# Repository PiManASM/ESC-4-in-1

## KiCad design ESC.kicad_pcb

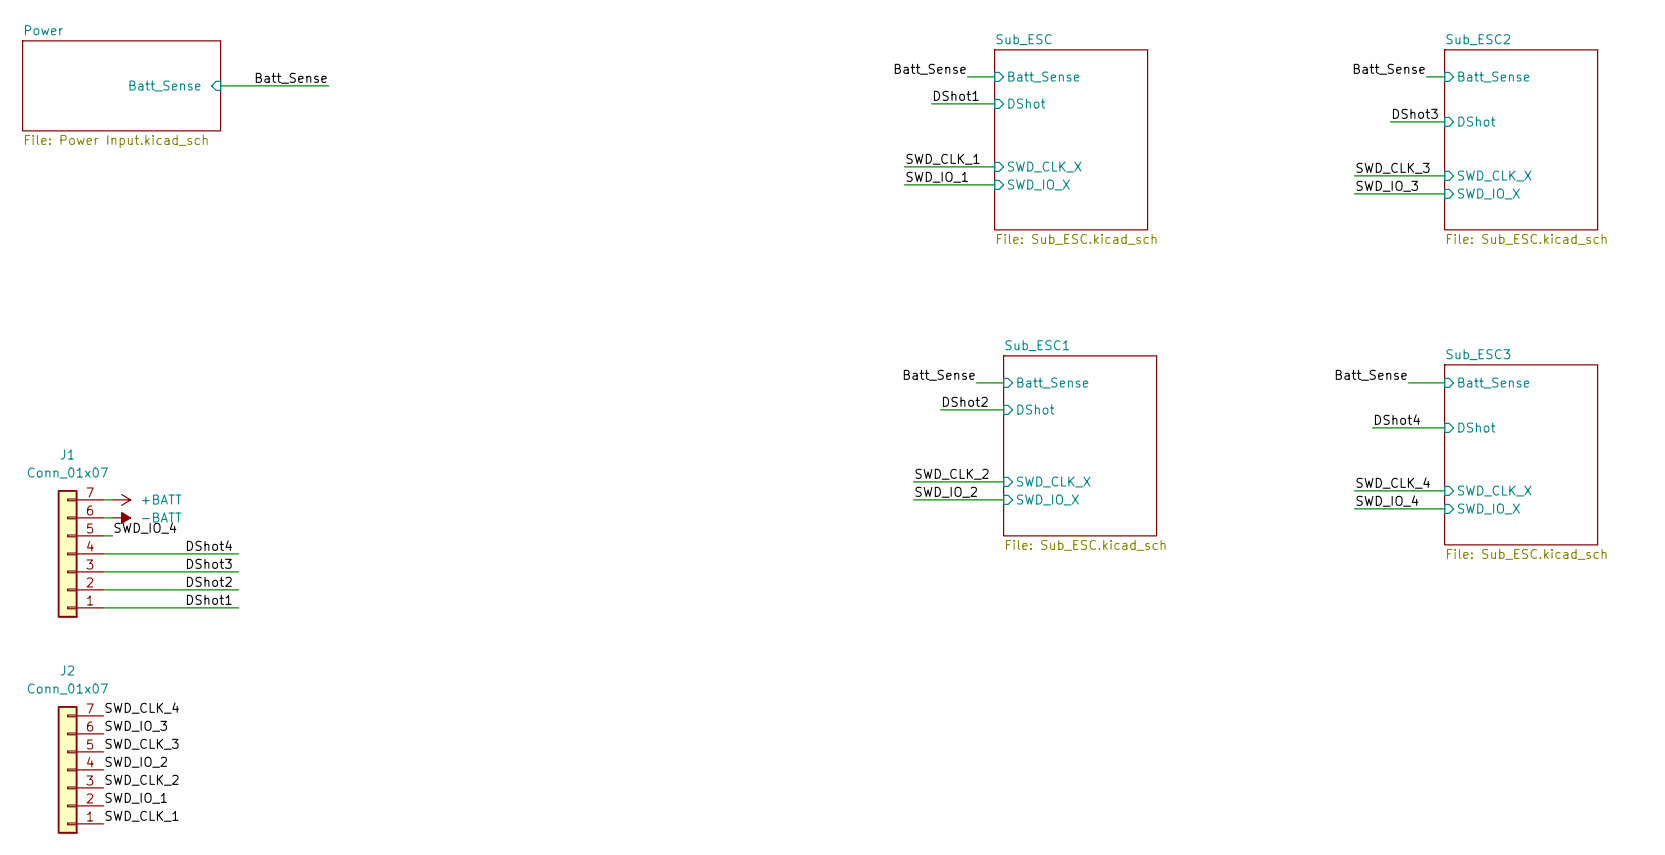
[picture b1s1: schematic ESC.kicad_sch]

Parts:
J1, J2: Conn_01x07; JST_GH_BM07B-GHS-TBT_1x07-1MP_P1.25mm_Vertical

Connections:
-BATT: J1.6; also elsewhere on the board
/DShot1: J1.1; also elsewhere on the board
/DShot2: J1.2; also elsewhere on the board
/DShot3: J1.3; also elsewhere on the board
/DShot4: J1.4; also elsewhere on the board
/SWD_CLK_1: J2.1; also elsewhere on the board
/SWD_CLK_2: J2.3; also elsewhere on the board
/SWD_CLK_3: J2.5; also elsewhere on the board
/SWD_CLK_4: J2.7; also elsewhere on the board
/SWD_IO_1: J2.2; also elsewhere on the board
/SWD_IO_2: J2.4; also elsewhere on the board
/SWD_IO_3: J2.6; also elsewhere on the board
/SWD_IO_4: J1.5; also elsewhere on the board

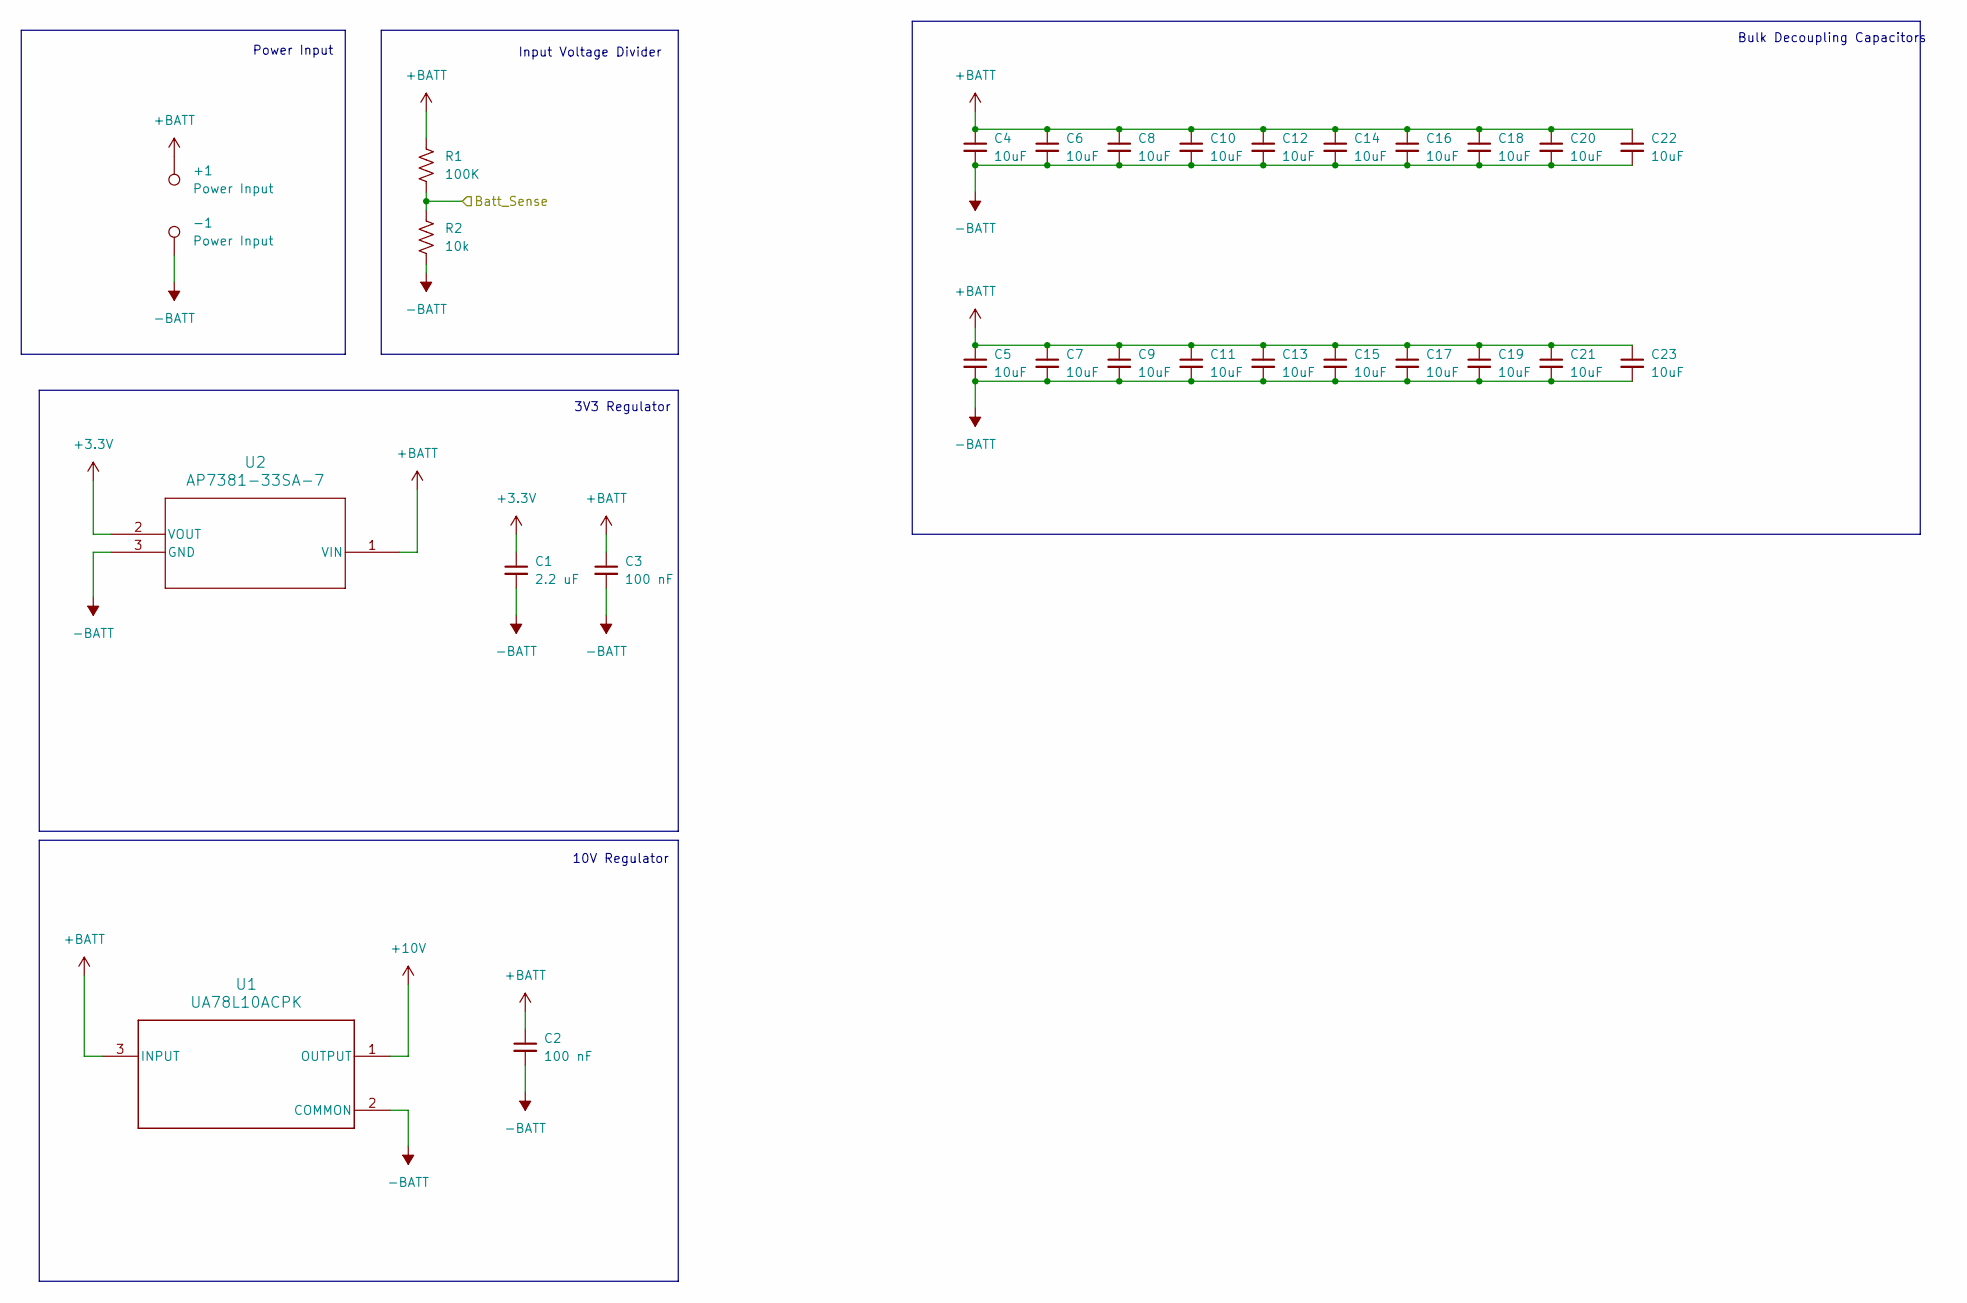
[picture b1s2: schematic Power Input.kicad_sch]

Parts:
+1: Power Input; TestPoint_Pad_4.0x4.0mm
-1: Power Input; TestPoint_Pad_4.0x4.0mm
C1: 2.2 uF; C_0402_1005Metric
C2, C3: 100 nF; C_0402_1005Metric
C4, C5, C6, C7, C8, C9, C10, C11, C12, C13, C14, C15, C16, C17, C18, C19, C20, C21, C22, C23: 10uF; C_0805_2012Metric
R1: 100K; R_0402_1005Metric
R2: 10k; R_0402_1005Metric
U1: UA78L10ACPK; PK0003A_L
U2: AP7381-33SA-7; SOT23_NONCALC_DIO

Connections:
+3.3V: C1.1, U2.2 (VOUT); also elsewhere on the board
-BATT: -1.1, C1.2, C2.2, C3.2, C4.2, C5.2, C6.2, C7.2, C8.2, C9.2, C10.2, C11.2, C12.2, C13.2, C14.2, C15.2, C16.2, C17.2, C18.2, C19.2, C20.2, C21.2, C22.2, C23.2, R2.2, U1.2 (COMMON), U2.3 (GND); also elsewhere on the board
/Batt_Sense: R1.2, R2.1; also elsewhere on the board

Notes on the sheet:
Bulk Decoupling Capacitors
Input Voltage Divider
10V Regulator
Power Input
3V3 Regulator

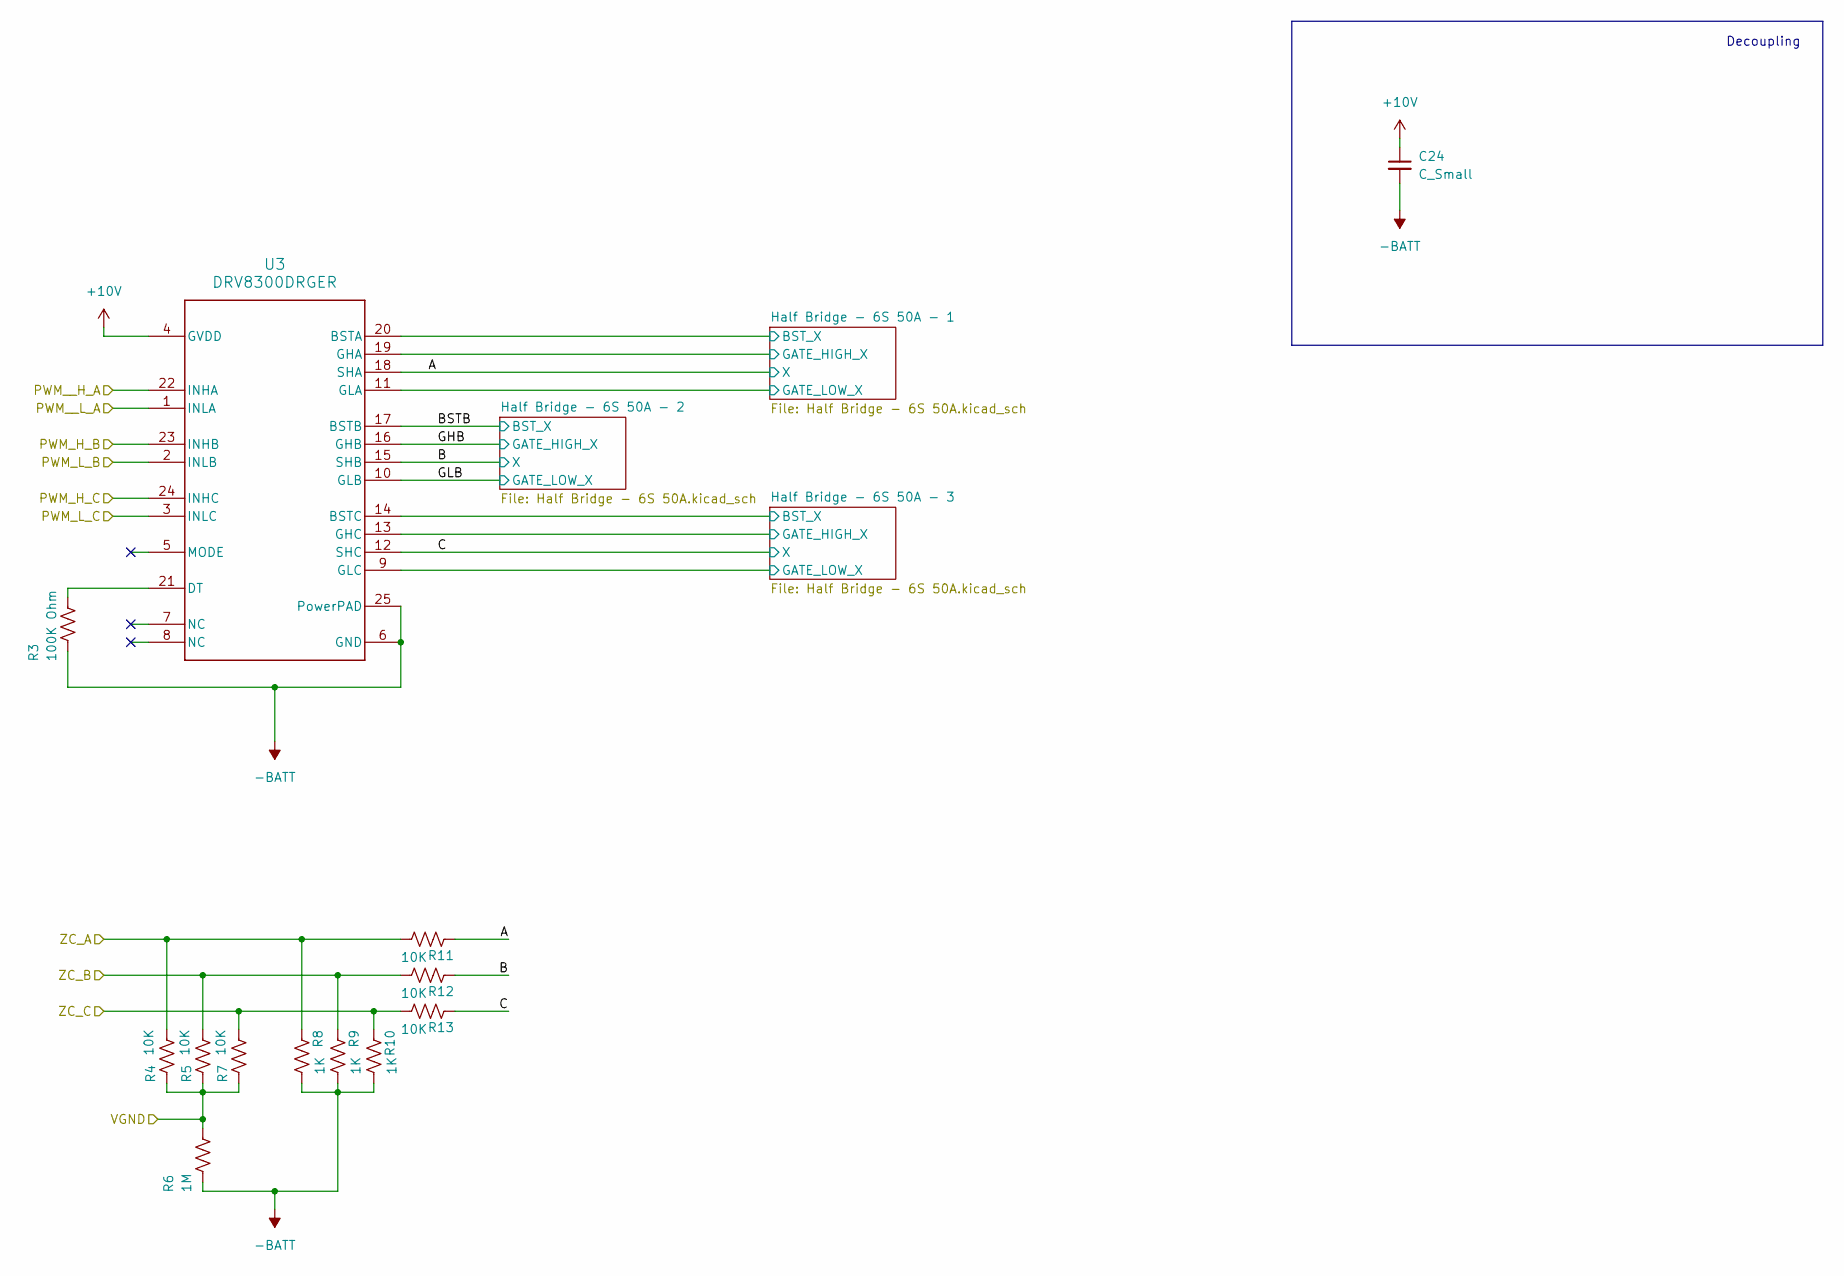
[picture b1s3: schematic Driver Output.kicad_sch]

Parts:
C24: C_Small; C_0603_1608Metric
R3: 100K Ohm; R_0402_1005Metric
R4, R5, R7, R11, R12, R13: 10K; R_0402_1005Metric
R6: 1M; R_0402_1005Metric
R8, R9, R10: 1K; R_0402_1005Metric
U3: DRV8300DRGER; RGE0024B-MFG

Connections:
-BATT: C24.2, R3.2, R6.2, R8.1, R9.1, R10.1, U3.6 (GND), U3.25 (PowerPAD), U3.26, U3.27, U3.28, U3.29, U3.30; also elsewhere on the board
/Sub_ESC/Driver Output/A: R11.2, U3.18 (SHA); also elsewhere on the board
/Sub_ESC/Driver Output/B: R12.2, U3.15 (SHB); also elsewhere on the board
/Sub_ESC/Driver Output/BSTB: U3.17 (BSTB); also elsewhere on the board
/Sub_ESC/Driver Output/C: R13.2, U3.12 (SHC); also elsewhere on the board
/Sub_ESC/Driver Output/GHB: U3.16 (GHB); also elsewhere on the board
/Sub_ESC/Driver Output/GLB: U3.10 (GLB); also elsewhere on the board
/Sub_ESC/Driver Output/Half Bridge - 6S 50A - 1/BST_X: U3.20 (BSTA); also elsewhere on the board
/Sub_ESC/Driver Output/Half Bridge - 6S 50A - 1/GATE_HIGH_X: U3.19 (GHA); also elsewhere on the board
/Sub_ESC/Driver Output/Half Bridge - 6S 50A - 1/GATE_LOW_X: U3.11 (GLA); also elsewhere on the board
/Sub_ESC/Driver Output/Half Bridge - 6S 50A - 3/BST_X: U3.14 (BSTC); also elsewhere on the board
/Sub_ESC/Driver Output/Half Bridge - 6S 50A - 3/GATE_HIGH_X: U3.13 (GHC); also elsewhere on the board
/Sub_ESC/Driver Output/Half Bridge - 6S 50A - 3/GATE_LOW_X: U3.9 (GLC); also elsewhere on the board
/Sub_ESC/Driver Output/PWM_H_B: U3.23 (INHB); also elsewhere on the board
/Sub_ESC/Driver Output/PWM_H_C: U3.24 (INHC); also elsewhere on the board
/Sub_ESC/Driver Output/PWM_L_B: U3.2 (INLB); also elsewhere on the board
/Sub_ESC/Driver Output/PWM_L_C: U3.3 (INLC); also elsewhere on the board
/Sub_ESC/Driver Output/PWM__H_A: U3.22 (INHA); also elsewhere on the board
/Sub_ESC/Driver Output/PWM__L_A: U3.1 (INLA); also elsewhere on the board
/Sub_ESC/Driver Output/ZC_A: R4.1, R8.2, R11.1; also elsewhere on the board
/Sub_ESC/Driver Output/ZC_B: R5.1, R9.2, R12.1; also elsewhere on the board
/Sub_ESC/Driver Output/ZC_C: R7.1, R10.2, R13.1; also elsewhere on the board
/Sub_ESC/VGND: R4.2, R5.2, R6.1, R7.2; also elsewhere on the board
unnamed: R3.1, U3.21 (DT)

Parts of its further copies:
C30, C37, C43: C_Small; C_0603_1608Metric
R16, R29, R42: 100K Ohm; R_0402_1005Metric
R17, R18, R20, R24, R25, R26, R30, R31, R33, R37, R38, R39, R43, R44, R46, R50, R51, R52: 10K; R_0402_1005Metric
R19, R32, R45: 1M; R_0402_1005Metric
R21, R22, R23, R34, R35, R36, R47, R48, R49: 1K; R_0402_1005Metric
U5, U7, U9: DRV8300DRGER; RGE0024B-MFG

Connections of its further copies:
-BATT: C30.2, C37.2, C43.2, R16.2, R19.2, R21.1, R22.1, R23.1, R29.2, R32.2, R34.1, R35.1, R36.1, R42.2, R45.2, R47.1, R48.1, R49.1, U5.6 (GND), U5.25 (PowerPAD), U5.26, U5.27, U5.28, U5.29, U5.30, U7.6 (GND), U7.25 (PowerPAD), U7.26, U7.27, U7.28, U7.29, U7.30, U9.6 (GND), U9.25 (PowerPAD), U9.26, U9.27, U9.28, U9.29, U9.30; also elsewhere on the board
/Sub_ESC1/Driver Output/A: R24.2, U5.18 (SHA); also elsewhere on the board
/Sub_ESC1/Driver Output/B: R25.2, U5.15 (SHB); also elsewhere on the board
/Sub_ESC1/Driver Output/BSTB: U5.17 (BSTB); also elsewhere on the board
/Sub_ESC1/Driver Output/C: R26.2, U5.12 (SHC); also elsewhere on the board
/Sub_ESC1/Driver Output/GHB: U5.16 (GHB); also elsewhere on the board
/Sub_ESC1/Driver Output/GLB: U5.10 (GLB); also elsewhere on the board
/Sub_ESC1/Driver Output/Half Bridge - 6S 50A - 1/BST_X: U5.20 (BSTA); also elsewhere on the board
/Sub_ESC1/Driver Output/Half Bridge - 6S 50A - 1/GATE_HIGH_X: U5.19 (GHA); also elsewhere on the board
/Sub_ESC1/Driver Output/Half Bridge - 6S 50A - 1/GATE_LOW_X: U5.11 (GLA); also elsewhere on the board
/Sub_ESC1/Driver Output/Half Bridge - 6S 50A - 3/BST_X: U5.14 (BSTC); also elsewhere on the board
/Sub_ESC1/Driver Output/Half Bridge - 6S 50A - 3/GATE_HIGH_X: U5.13 (GHC); also elsewhere on the board
/Sub_ESC1/Driver Output/Half Bridge - 6S 50A - 3/GATE_LOW_X: U5.9 (GLC); also elsewhere on the board
/Sub_ESC1/Driver Output/PWM_H_B: U5.23 (INHB); also elsewhere on the board
/Sub_ESC1/Driver Output/PWM_H_C: U5.24 (INHC); also elsewhere on the board
/Sub_ESC1/Driver Output/PWM_L_B: U5.2 (INLB); also elsewhere on the board
/Sub_ESC1/Driver Output/PWM_L_C: U5.3 (INLC); also elsewhere on the board
/Sub_ESC1/Driver Output/PWM__H_A: U5.22 (INHA); also elsewhere on the board
/Sub_ESC1/Driver Output/PWM__L_A: U5.1 (INLA); also elsewhere on the board
/Sub_ESC1/Driver Output/ZC_A: R17.1, R21.2, R24.1; also elsewhere on the board
/Sub_ESC1/Driver Output/ZC_B: R18.1, R22.2, R25.1; also elsewhere on the board
/Sub_ESC1/Driver Output/ZC_C: R20.1, R23.2, R26.1; also elsewhere on the board
/Sub_ESC1/VGND: R17.2, R18.2, R19.1, R20.2; also elsewhere on the board
/Sub_ESC2/Driver Output/A: R37.2, U7.18 (SHA); also elsewhere on the board
/Sub_ESC2/Driver Output/B: R38.2, U7.15 (SHB); also elsewhere on the board
/Sub_ESC2/Driver Output/BSTB: U7.17 (BSTB); also elsewhere on the board
/Sub_ESC2/Driver Output/C: R39.2, U7.12 (SHC); also elsewhere on the board
/Sub_ESC2/Driver Output/GHB: U7.16 (GHB); also elsewhere on the board
/Sub_ESC2/Driver Output/GLB: U7.10 (GLB); also elsewhere on the board
/Sub_ESC2/Driver Output/Half Bridge - 6S 50A - 1/BST_X: U7.20 (BSTA); also elsewhere on the board
/Sub_ESC2/Driver Output/Half Bridge - 6S 50A - 1/GATE_HIGH_X: U7.19 (GHA); also elsewhere on the board
/Sub_ESC2/Driver Output/Half Bridge - 6S 50A - 1/GATE_LOW_X: U7.11 (GLA); also elsewhere on the board
/Sub_ESC2/Driver Output/Half Bridge - 6S 50A - 3/BST_X: U7.14 (BSTC); also elsewhere on the board
/Sub_ESC2/Driver Output/Half Bridge - 6S 50A - 3/GATE_HIGH_X: U7.13 (GHC); also elsewhere on the board
/Sub_ESC2/Driver Output/Half Bridge - 6S 50A - 3/GATE_LOW_X: U7.9 (GLC); also elsewhere on the board
/Sub_ESC2/Driver Output/PWM_H_B: U7.23 (INHB); also elsewhere on the board
/Sub_ESC2/Driver Output/PWM_H_C: U7.24 (INHC); also elsewhere on the board
/Sub_ESC2/Driver Output/PWM_L_B: U7.2 (INLB); also elsewhere on the board
/Sub_ESC2/Driver Output/PWM_L_C: U7.3 (INLC); also elsewhere on the board
/Sub_ESC2/Driver Output/PWM__H_A: U7.22 (INHA); also elsewhere on the board
/Sub_ESC2/Driver Output/PWM__L_A: U7.1 (INLA); also elsewhere on the board
/Sub_ESC2/Driver Output/ZC_A: R30.1, R34.2, R37.1; also elsewhere on the board
/Sub_ESC2/Driver Output/ZC_B: R31.1, R35.2, R38.1; also elsewhere on the board
/Sub_ESC2/Driver Output/ZC_C: R33.1, R36.2, R39.1; also elsewhere on the board
/Sub_ESC2/VGND: R30.2, R31.2, R32.1, R33.2; also elsewhere on the board
/Sub_ESC3/Driver Output/A: R50.2, U9.18 (SHA); also elsewhere on the board
/Sub_ESC3/Driver Output/B: R51.2, U9.15 (SHB); also elsewhere on the board
/Sub_ESC3/Driver Output/BSTB: U9.17 (BSTB); also elsewhere on the board
/Sub_ESC3/Driver Output/C: R52.2, U9.12 (SHC); also elsewhere on the board
/Sub_ESC3/Driver Output/GHB: U9.16 (GHB); also elsewhere on the board
/Sub_ESC3/Driver Output/GLB: U9.10 (GLB); also elsewhere on the board
/Sub_ESC3/Driver Output/Half Bridge - 6S 50A - 1/BST_X: U9.20 (BSTA); also elsewhere on the board
/Sub_ESC3/Driver Output/Half Bridge - 6S 50A - 1/GATE_HIGH_X: U9.19 (GHA); also elsewhere on the board
/Sub_ESC3/Driver Output/Half Bridge - 6S 50A - 1/GATE_LOW_X: U9.11 (GLA); also elsewhere on the board
/Sub_ESC3/Driver Output/Half Bridge - 6S 50A - 3/BST_X: U9.14 (BSTC); also elsewhere on the board
/Sub_ESC3/Driver Output/Half Bridge - 6S 50A - 3/GATE_HIGH_X: U9.13 (GHC); also elsewhere on the board
/Sub_ESC3/Driver Output/Half Bridge - 6S 50A - 3/GATE_LOW_X: U9.9 (GLC); also elsewhere on the board
/Sub_ESC3/Driver Output/PWM_H_B: U9.23 (INHB); also elsewhere on the board
/Sub_ESC3/Driver Output/PWM_H_C: U9.24 (INHC); also elsewhere on the board
/Sub_ESC3/Driver Output/PWM_L_B: U9.2 (INLB); also elsewhere on the board
/Sub_ESC3/Driver Output/PWM_L_C: U9.3 (INLC); also elsewhere on the board
/Sub_ESC3/Driver Output/PWM__H_A: U9.22 (INHA); also elsewhere on the board
/Sub_ESC3/Driver Output/PWM__L_A: U9.1 (INLA); also elsewhere on the board
/Sub_ESC3/Driver Output/ZC_A: R43.1, R47.2, R50.1; also elsewhere on the board
/Sub_ESC3/Driver Output/ZC_B: R44.1, R48.2, R51.1; also elsewhere on the board
/Sub_ESC3/Driver Output/ZC_C: R46.1, R49.2, R52.1; also elsewhere on the board
/Sub_ESC3/VGND: R43.2, R44.2, R45.1, R46.2; also elsewhere on the board
unnamed: R16.1, U5.21 (DT)
unnamed: R29.1, U7.21 (DT)
unnamed: R42.1, U9.21 (DT)

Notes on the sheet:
Decoupling

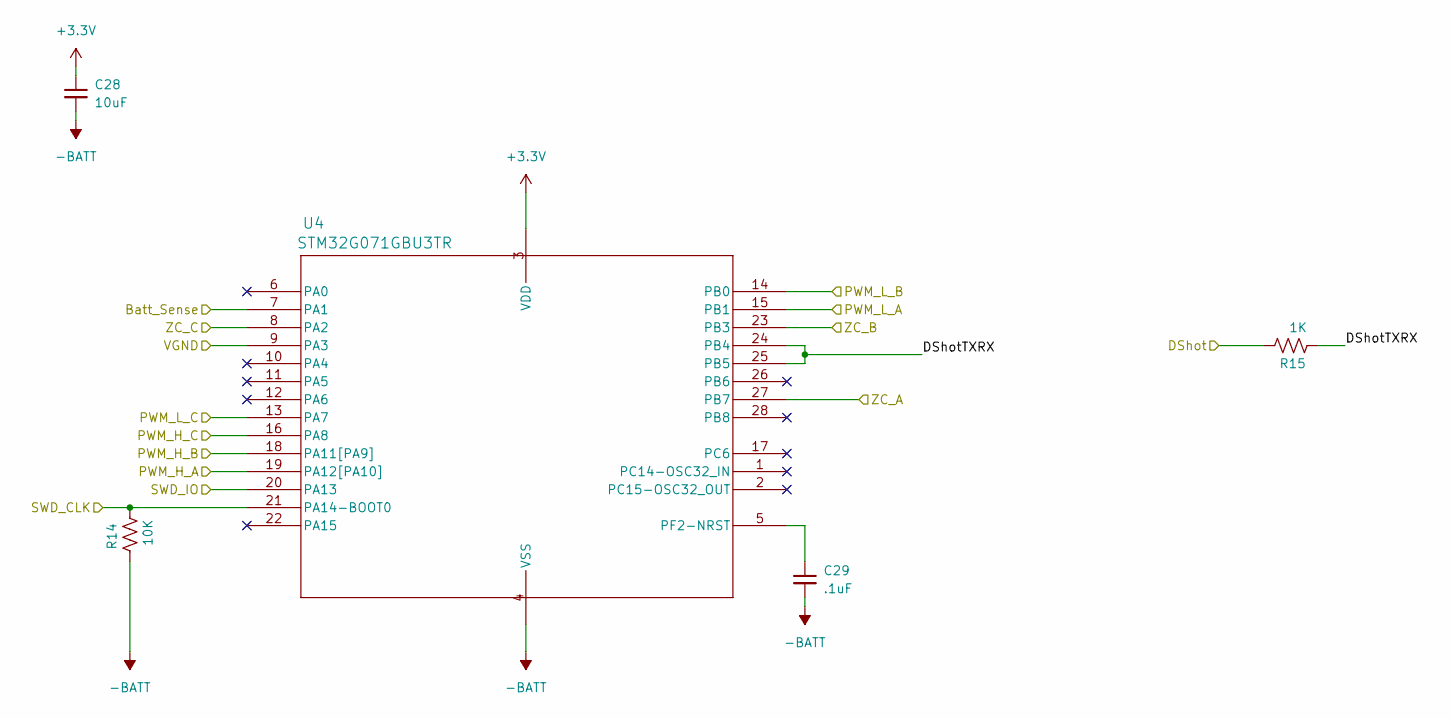
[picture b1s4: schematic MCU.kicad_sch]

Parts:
C28: 10uF; C_0402_1005Metric
C29: .1uF; C_0402_1005Metric
R14: 10K; R_0402_1005Metric
R15: 1K; R_0402_1005Metric
U4: STM32G071GBU3TR; UFQFPN-28

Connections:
+3.3V: C28.1, U4.3 (VDD); also elsewhere on the board
-BATT: C28.2, C29.2, R14.1, U4.4 (VSS); also elsewhere on the board
/Batt_Sense: U4.7 (PA1); also elsewhere on the board
/DShot1: R15.2; also elsewhere on the board
/SWD_CLK_1: R14.2, U4.21 (PA14-BOOT0); also elsewhere on the board
/SWD_IO_1: U4.20 (PA13); also elsewhere on the board
/Sub_ESC/Driver Output/PWM_H_B: U4.18 (PA11[PA9]); also elsewhere on the board
/Sub_ESC/Driver Output/PWM_H_C: U4.16 (PA8); also elsewhere on the board
/Sub_ESC/Driver Output/PWM_L_B: U4.14 (PB0); also elsewhere on the board
/Sub_ESC/Driver Output/PWM_L_C: U4.13 (PA7); also elsewhere on the board
/Sub_ESC/Driver Output/PWM__H_A: U4.19 (PA12[PA10]); also elsewhere on the board
/Sub_ESC/Driver Output/PWM__L_A: U4.15 (PB1); also elsewhere on the board
/Sub_ESC/Driver Output/ZC_A: U4.27 (PB7); also elsewhere on the board
/Sub_ESC/Driver Output/ZC_B: U4.23 (PB3); also elsewhere on the board
/Sub_ESC/Driver Output/ZC_C: U4.8 (PA2); also elsewhere on the board
/Sub_ESC/MCU/DShotTXRX: R15.1, U4.24 (PB4), U4.25 (PB5)
/Sub_ESC/VGND: U4.9 (PA3); also elsewhere on the board
unnamed: C29.1, U4.5 (PF2-NRST)

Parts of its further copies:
C35, C41, C47: 10uF; C_0402_1005Metric
C36, C42, C48: .1uF; C_0402_1005Metric
R27, R40, R53: 10K; R_0402_1005Metric
R28, R41, R54: 1K; R_0402_1005Metric
U6, U8, U10: STM32G071GBU3TR; UFQFPN-28

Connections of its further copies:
+3.3V: C35.1, C41.1, C47.1, U6.3 (VDD), U8.3 (VDD), U10.3 (VDD); also elsewhere on the board
-BATT: C35.2, C36.2, C41.2, C42.2, C47.2, C48.2, R27.1, R40.1, R53.1, U6.4 (VSS), U8.4 (VSS), U10.4 (VSS); also elsewhere on the board
/Batt_Sense: U6.7 (PA1), U8.7 (PA1), U10.7 (PA1); also elsewhere on the board
/DShot2: R28.2; also elsewhere on the board
/DShot3: R41.2; also elsewhere on the board
/DShot4: R54.2; also elsewhere on the board
/SWD_CLK_2: R27.2, U6.21 (PA14-BOOT0); also elsewhere on the board
/SWD_CLK_3: R40.2, U8.21 (PA14-BOOT0); also elsewhere on the board
/SWD_CLK_4: R53.2, U10.21 (PA14-BOOT0); also elsewhere on the board
/SWD_IO_2: U6.20 (PA13); also elsewhere on the board
/SWD_IO_3: U8.20 (PA13); also elsewhere on the board
/SWD_IO_4: U10.20 (PA13); also elsewhere on the board
/Sub_ESC1/Driver Output/PWM_H_B: U6.18 (PA11[PA9]); also elsewhere on the board
/Sub_ESC1/Driver Output/PWM_H_C: U6.16 (PA8); also elsewhere on the board
/Sub_ESC1/Driver Output/PWM_L_B: U6.14 (PB0); also elsewhere on the board
/Sub_ESC1/Driver Output/PWM_L_C: U6.13 (PA7); also elsewhere on the board
/Sub_ESC1/Driver Output/PWM__H_A: U6.19 (PA12[PA10]); also elsewhere on the board
/Sub_ESC1/Driver Output/PWM__L_A: U6.15 (PB1); also elsewhere on the board
/Sub_ESC1/Driver Output/ZC_A: U6.27 (PB7); also elsewhere on the board
/Sub_ESC1/Driver Output/ZC_B: U6.23 (PB3); also elsewhere on the board
/Sub_ESC1/Driver Output/ZC_C: U6.8 (PA2); also elsewhere on the board
/Sub_ESC1/MCU/DShotTXRX: R28.1, U6.24 (PB4), U6.25 (PB5)
/Sub_ESC1/VGND: U6.9 (PA3); also elsewhere on the board
/Sub_ESC2/Driver Output/PWM_H_B: U8.18 (PA11[PA9]); also elsewhere on the board
/Sub_ESC2/Driver Output/PWM_H_C: U8.16 (PA8); also elsewhere on the board
/Sub_ESC2/Driver Output/PWM_L_B: U8.14 (PB0); also elsewhere on the board
/Sub_ESC2/Driver Output/PWM_L_C: U8.13 (PA7); also elsewhere on the board
/Sub_ESC2/Driver Output/PWM__H_A: U8.19 (PA12[PA10]); also elsewhere on the board
/Sub_ESC2/Driver Output/PWM__L_A: U8.15 (PB1); also elsewhere on the board
/Sub_ESC2/Driver Output/ZC_A: U8.27 (PB7); also elsewhere on the board
/Sub_ESC2/Driver Output/ZC_B: U8.23 (PB3); also elsewhere on the board
/Sub_ESC2/Driver Output/ZC_C: U8.8 (PA2); also elsewhere on the board
/Sub_ESC2/MCU/DShotTXRX: R41.1, U8.24 (PB4), U8.25 (PB5)
/Sub_ESC2/VGND: U8.9 (PA3); also elsewhere on the board
/Sub_ESC3/Driver Output/PWM_H_B: U10.18 (PA11[PA9]); also elsewhere on the board
/Sub_ESC3/Driver Output/PWM_H_C: U10.16 (PA8); also elsewhere on the board
/Sub_ESC3/Driver Output/PWM_L_B: U10.14 (PB0); also elsewhere on the board
/Sub_ESC3/Driver Output/PWM_L_C: U10.13 (PA7); also elsewhere on the board
/Sub_ESC3/Driver Output/PWM__H_A: U10.19 (PA12[PA10]); also elsewhere on the board
/Sub_ESC3/Driver Output/PWM__L_A: U10.15 (PB1); also elsewhere on the board
/Sub_ESC3/Driver Output/ZC_A: U10.27 (PB7); also elsewhere on the board
/Sub_ESC3/Driver Output/ZC_B: U10.23 (PB3); also elsewhere on the board
/Sub_ESC3/Driver Output/ZC_C: U10.8 (PA2); also elsewhere on the board
/Sub_ESC3/MCU/DShotTXRX: R54.1, U10.24 (PB4), U10.25 (PB5)
/Sub_ESC3/VGND: U10.9 (PA3); also elsewhere on the board
unnamed: C36.1, U6.5 (PF2-NRST)
unnamed: C42.1, U8.5 (PF2-NRST)
unnamed: C48.1, U10.5 (PF2-NRST)

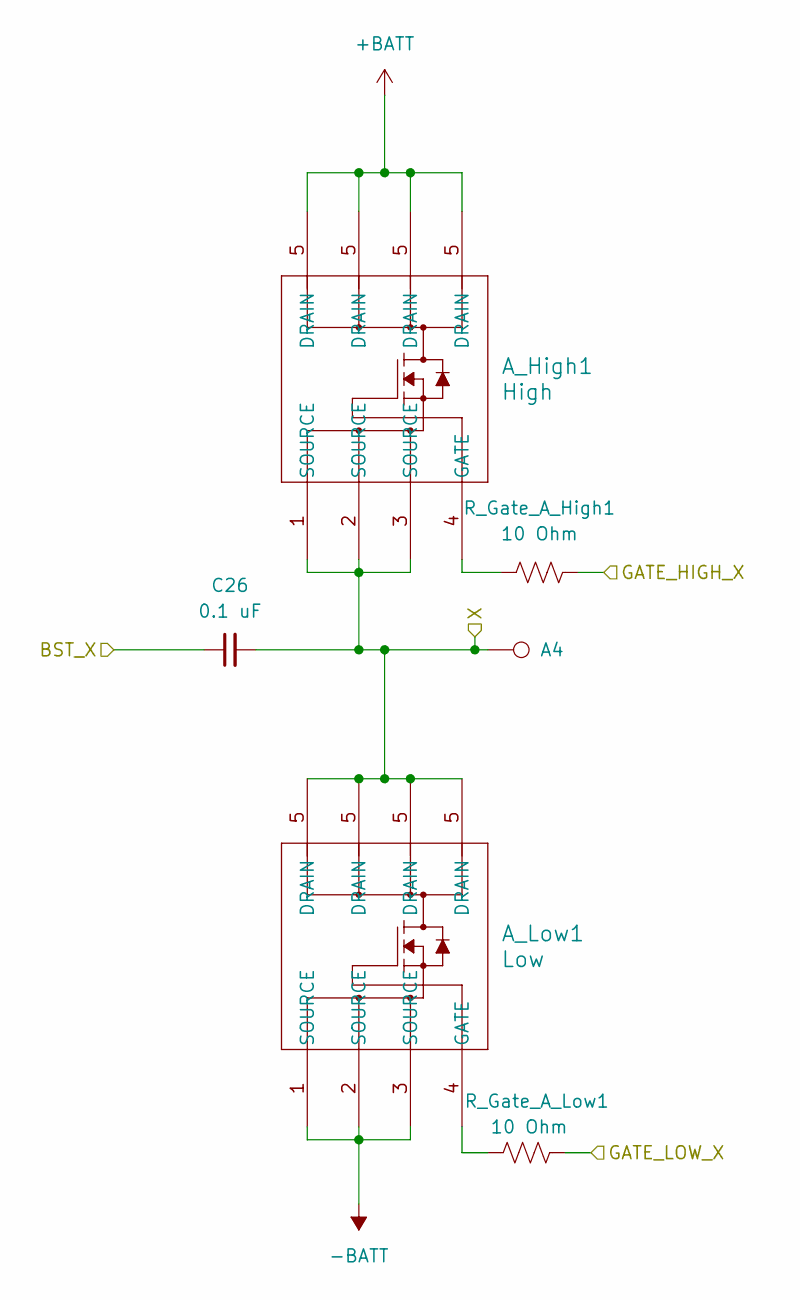
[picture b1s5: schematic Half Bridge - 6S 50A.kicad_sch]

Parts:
A4: TestPoint; TestPoint_Pad_3.5x2.0mm
A_High1: High; SOP-ADVANCE_N_TOS
A_Low1: Low; SOP-ADVANCE_N_TOS
C26: 0.1 uF; C_0402_1005Metric
R_Gate_A_High1: 10 Ohm; R_0402_1005Metric
R_Gate_A_Low1: 10 Ohm; R_0402_1005Metric

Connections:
-BATT: A_Low1.1 (SOURCE), A_Low1.2 (SOURCE), A_Low1.3 (SOURCE); also elsewhere on the board
/Sub_ESC/Driver Output/A: A_High1.1 (SOURCE), A_High1.2 (SOURCE), A_High1.3 (SOURCE), A_Low1.5 (DRAIN), C26.2; also elsewhere on the board
/Sub_ESC/Driver Output/Half Bridge - 6S 50A - 1/BST_X: C26.1; also elsewhere on the board
/Sub_ESC/Driver Output/Half Bridge - 6S 50A - 1/GATE_HIGH_X: R_Gate_A_High1.1; also elsewhere on the board
/Sub_ESC/Driver Output/Half Bridge - 6S 50A - 1/GATE_LOW_X: R_Gate_A_Low1.1; also elsewhere on the board
unnamed: A_High1.4 (GATE), R_Gate_A_High1.2
unnamed: A_Low1.4 (GATE), R_Gate_A_Low1.2

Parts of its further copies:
A1, A2, A3: TestPoint; TestPoint_Pad_3.5x2.0mm
A_High2, A_High3, A_High4: High; SOP-ADVANCE_N_TOS
A_Low2, A_Low3, A_Low4: Low; SOP-ADVANCE_N_TOS
B_High1, B_High2, B_High3, B_High4: High; SOP-ADVANCE_N_TOS
B_Low1, B_Low2, B_Low3, B_Low4: Low; SOP-ADVANCE_N_TOS
C25, C27, C31, C32, C34, C38, C39, C40, C44, C45, C46: 0.1 uF; C_0402_1005Metric
C_High1, C_High2, C_High3, C_High4: High; SOP-ADVANCE_N_TOS
C_Low1, C_Low2, C_Low3, C_Low4: Low; SOP-ADVANCE_N_TOS
R_Gate_A_High2, R_Gate_A_High3, R_Gate_A_High4: 10 Ohm; R_0402_1005Metric
R_Gate_A_Low2, R_Gate_A_Low3, R_Gate_A_Low4: 10 Ohm; R_0402_1005Metric
R_Gate_B_High1, R_Gate_B_High2, R_Gate_B_High3, R_Gate_B_High4: 10 Ohm; R_0402_1005Metric
R_Gate_B_Low1, R_Gate_B_Low2, R_Gate_B_Low3, R_Gate_B_Low4: 10 Ohm; R_0402_1005Metric
R_Gate_C_High1, R_Gate_C_High2, R_Gate_C_High3, R_Gate_C_High4: 10 Ohm; R_0402_1005Metric
R_Gate_C_Low1, R_Gate_C_Low2, R_Gate_C_Low3, R_Gate_C_Low4: 10 Ohm; R_0402_1005Metric

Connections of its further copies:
-BATT: A_Low2.1 (SOURCE), A_Low2.2 (SOURCE), A_Low2.3 (SOURCE), A_Low3.1 (SOURCE), A_Low3.2 (SOURCE), A_Low3.3 (SOURCE), A_Low4.1 (SOURCE), A_Low4.2 (SOURCE), A_Low4.3 (SOURCE), B_Low1.1 (SOURCE), B_Low1.2 (SOURCE), B_Low1.3 (SOURCE), B_Low2.1 (SOURCE), B_Low2.2 (SOURCE), B_Low2.3 (SOURCE), B_Low3.1 (SOURCE), B_Low3.2 (SOURCE), B_Low3.3 (SOURCE), B_Low4.1 (SOURCE), B_Low4.2 (SOURCE), B_Low4.3 (SOURCE), C_Low1.1 (SOURCE), C_Low1.2 (SOURCE), C_Low1.3 (SOURCE), C_Low2.1 (SOURCE), C_Low2.2 (SOURCE), C_Low2.3 (SOURCE), C_Low3.1 (SOURCE), C_Low3.2 (SOURCE), C_Low3.3 (SOURCE), C_Low4.1 (SOURCE), C_Low4.2 (SOURCE), C_Low4.3 (SOURCE); also elsewhere on the board
/Sub_ESC1/Driver Output/A: A_High2.1 (SOURCE), A_High2.2 (SOURCE), A_High2.3 (SOURCE), A_Low2.5 (DRAIN), C31.2; also elsewhere on the board
/Sub_ESC1/Driver Output/B: B_High2.1 (SOURCE), B_High2.2 (SOURCE), B_High2.3 (SOURCE), B_Low2.5 (DRAIN), C34.2; also elsewhere on the board
/Sub_ESC1/Driver Output/BSTB: C34.1; also elsewhere on the board
/Sub_ESC1/Driver Output/C: C32.2, C_High2.1 (SOURCE), C_High2.2 (SOURCE), C_High2.3 (SOURCE), C_Low2.5 (DRAIN); also elsewhere on the board
/Sub_ESC1/Driver Output/GHB: R_Gate_B_High2.1; also elsewhere on the board
/Sub_ESC1/Driver Output/GLB: R_Gate_B_Low2.1; also elsewhere on the board
/Sub_ESC1/Driver Output/Half Bridge - 6S 50A - 1/BST_X: C31.1; also elsewhere on the board
/Sub_ESC1/Driver Output/Half Bridge - 6S 50A - 1/GATE_HIGH_X: R_Gate_A_High2.1; also elsewhere on the board
/Sub_ESC1/Driver Output/Half Bridge - 6S 50A - 1/GATE_LOW_X: R_Gate_A_Low2.1; also elsewhere on the board
/Sub_ESC1/Driver Output/Half Bridge - 6S 50A - 3/BST_X: C32.1; also elsewhere on the board
/Sub_ESC1/Driver Output/Half Bridge - 6S 50A - 3/GATE_HIGH_X: R_Gate_C_High2.1; also elsewhere on the board
/Sub_ESC1/Driver Output/Half Bridge - 6S 50A - 3/GATE_LOW_X: R_Gate_C_Low2.1; also elsewhere on the board
/Sub_ESC2/Driver Output/A: A_High3.1 (SOURCE), A_High3.2 (SOURCE), A_High3.3 (SOURCE), A_Low3.5 (DRAIN), C38.2; also elsewhere on the board
/Sub_ESC2/Driver Output/B: B_High3.1 (SOURCE), B_High3.2 (SOURCE), B_High3.3 (SOURCE), B_Low3.5 (DRAIN), C40.2; also elsewhere on the board
/Sub_ESC2/Driver Output/BSTB: C40.1; also elsewhere on the board
/Sub_ESC2/Driver Output/C: C39.2, C_High3.1 (SOURCE), C_High3.2 (SOURCE), C_High3.3 (SOURCE), C_Low3.5 (DRAIN); also elsewhere on the board
/Sub_ESC2/Driver Output/GHB: R_Gate_B_High3.1; also elsewhere on the board
/Sub_ESC2/Driver Output/GLB: R_Gate_B_Low3.1; also elsewhere on the board
/Sub_ESC2/Driver Output/Half Bridge - 6S 50A - 1/BST_X: C38.1; also elsewhere on the board
/Sub_ESC2/Driver Output/Half Bridge - 6S 50A - 1/GATE_HIGH_X: R_Gate_A_High3.1; also elsewhere on the board
/Sub_ESC2/Driver Output/Half Bridge - 6S 50A - 1/GATE_LOW_X: R_Gate_A_Low3.1; also elsewhere on the board
/Sub_ESC2/Driver Output/Half Bridge - 6S 50A - 3/BST_X: C39.1; also elsewhere on the board
/Sub_ESC2/Driver Output/Half Bridge - 6S 50A - 3/GATE_HIGH_X: R_Gate_C_High3.1; also elsewhere on the board
/Sub_ESC2/Driver Output/Half Bridge - 6S 50A - 3/GATE_LOW_X: R_Gate_C_Low3.1; also elsewhere on the board
/Sub_ESC3/Driver Output/A: A_High4.1 (SOURCE), A_High4.2 (SOURCE), A_High4.3 (SOURCE), A_Low4.5 (DRAIN), C44.2; also elsewhere on the board
/Sub_ESC3/Driver Output/B: B_High4.1 (SOURCE), B_High4.2 (SOURCE), B_High4.3 (SOURCE), B_Low4.5 (DRAIN), C46.2; also elsewhere on the board
/Sub_ESC3/Driver Output/BSTB: C46.1; also elsewhere on the board
/Sub_ESC3/Driver Output/C: C45.2, C_High4.1 (SOURCE), C_High4.2 (SOURCE), C_High4.3 (SOURCE), C_Low4.5 (DRAIN); also elsewhere on the board
/Sub_ESC3/Driver Output/GHB: R_Gate_B_High4.1; also elsewhere on the board
/Sub_ESC3/Driver Output/GLB: R_Gate_B_Low4.1; also elsewhere on the board
/Sub_ESC3/Driver Output/Half Bridge - 6S 50A - 1/BST_X: C44.1; also elsewhere on the board
/Sub_ESC3/Driver Output/Half Bridge - 6S 50A - 1/GATE_HIGH_X: R_Gate_A_High4.1; also elsewhere on the board
/Sub_ESC3/Driver Output/Half Bridge - 6S 50A - 1/GATE_LOW_X: R_Gate_A_Low4.1; also elsewhere on the board
/Sub_ESC3/Driver Output/Half Bridge - 6S 50A - 3/BST_X: C45.1; also elsewhere on the board
/Sub_ESC3/Driver Output/Half Bridge - 6S 50A - 3/GATE_HIGH_X: R_Gate_C_High4.1; also elsewhere on the board
/Sub_ESC3/Driver Output/Half Bridge - 6S 50A - 3/GATE_LOW_X: R_Gate_C_Low4.1; also elsewhere on the board
/Sub_ESC/Driver Output/A: A2.1; also elsewhere on the board
/Sub_ESC/Driver Output/B: A3.1, B_High1.1 (SOURCE), B_High1.2 (SOURCE), B_High1.3 (SOURCE), B_Low1.5 (DRAIN), C27.2; also elsewhere on the board
/Sub_ESC/Driver Output/BSTB: C27.1; also elsewhere on the board
/Sub_ESC/Driver Output/C: A1.1, C25.2, C_High1.1 (SOURCE), C_High1.2 (SOURCE), C_High1.3 (SOURCE), C_Low1.5 (DRAIN); also elsewhere on the board
/Sub_ESC/Driver Output/GHB: R_Gate_B_High1.1; also elsewhere on the board
/Sub_ESC/Driver Output/GLB: R_Gate_B_Low1.1; also elsewhere on the board
/Sub_ESC/Driver Output/Half Bridge - 6S 50A - 3/BST_X: C25.1; also elsewhere on the board
/Sub_ESC/Driver Output/Half Bridge - 6S 50A - 3/GATE_HIGH_X: R_Gate_C_High1.1; also elsewhere on the board
/Sub_ESC/Driver Output/Half Bridge - 6S 50A - 3/GATE_LOW_X: R_Gate_C_Low1.1; also elsewhere on the board
unnamed: A_High2.4 (GATE), R_Gate_A_High2.2
unnamed: A_High3.4 (GATE), R_Gate_A_High3.2
unnamed: A_High4.4 (GATE), R_Gate_A_High4.2
unnamed: A_Low2.4 (GATE), R_Gate_A_Low2.2
unnamed: A_Low3.4 (GATE), R_Gate_A_Low3.2
unnamed: A_Low4.4 (GATE), R_Gate_A_Low4.2
unnamed: B_High1.4 (GATE), R_Gate_B_High1.2
unnamed: B_High2.4 (GATE), R_Gate_B_High2.2
unnamed: B_High3.4 (GATE), R_Gate_B_High3.2
unnamed: B_High4.4 (GATE), R_Gate_B_High4.2
unnamed: B_Low1.4 (GATE), R_Gate_B_Low1.2
unnamed: B_Low2.4 (GATE), R_Gate_B_Low2.2
unnamed: B_Low3.4 (GATE), R_Gate_B_Low3.2
unnamed: B_Low4.4 (GATE), R_Gate_B_Low4.2
unnamed: C_High1.4 (GATE), R_Gate_C_High1.2
unnamed: C_High2.4 (GATE), R_Gate_C_High2.2
unnamed: C_High3.4 (GATE), R_Gate_C_High3.2
unnamed: C_High4.4 (GATE), R_Gate_C_High4.2
unnamed: C_Low1.4 (GATE), R_Gate_C_Low1.2
unnamed: C_Low2.4 (GATE), R_Gate_C_Low2.2
unnamed: C_Low3.4 (GATE), R_Gate_C_Low3.2
unnamed: C_Low4.4 (GATE), R_Gate_C_Low4.2

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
